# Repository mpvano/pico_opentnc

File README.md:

# PICO_OPENTNC

This is a fork of Peter Filberti's excellent TNC project modified to allow his code to run on the openTNC hardware reference design. This way either firmware can be used on that hardware merely by swapping preprogammed microcontrollers. Note that this fork is for the Pi Pico 2040 only.

# PICO TNC

PICO TNC is the Terminal Node Controler for Amateur Packet Radio powered by Raspberry Pi Pico. This is a fork of that project. I have removed all of the major features of the code except for the modulator/demodulator section and inserted a z80 emulator from my TNCEMU project that emulates a Heathkit HK21 Pocket Packet. Introductory Video can be seen here: https://youtu.be/zq6JLoosqGQ

## PIC TNC features

- Encode and decode Bell 202 AFSK signal without modem chip
- Support USB Serial as well as 3.3v ttl serial interface
- Emulated Support of full tnc and tnc commands including pbbs
- Kiss support at the flip of a switch.
- Operates with open squelch
- TTL Serial Port is configured by emulated TNC parameters when used as a console port.

## Todo
- Add 1600 1800 hz modem for HF Modem support.
- Investigate if FX.25 can be added especially for hf.

## How to build
```
git clone https://github.com/mpvano/pico_opentnc.git
cd pico_opentnc
mkdir build
cd build
cmake ..
make -j4
(flash 'pico_tnc/pico_tnc.uf2' file to your Pico)
```

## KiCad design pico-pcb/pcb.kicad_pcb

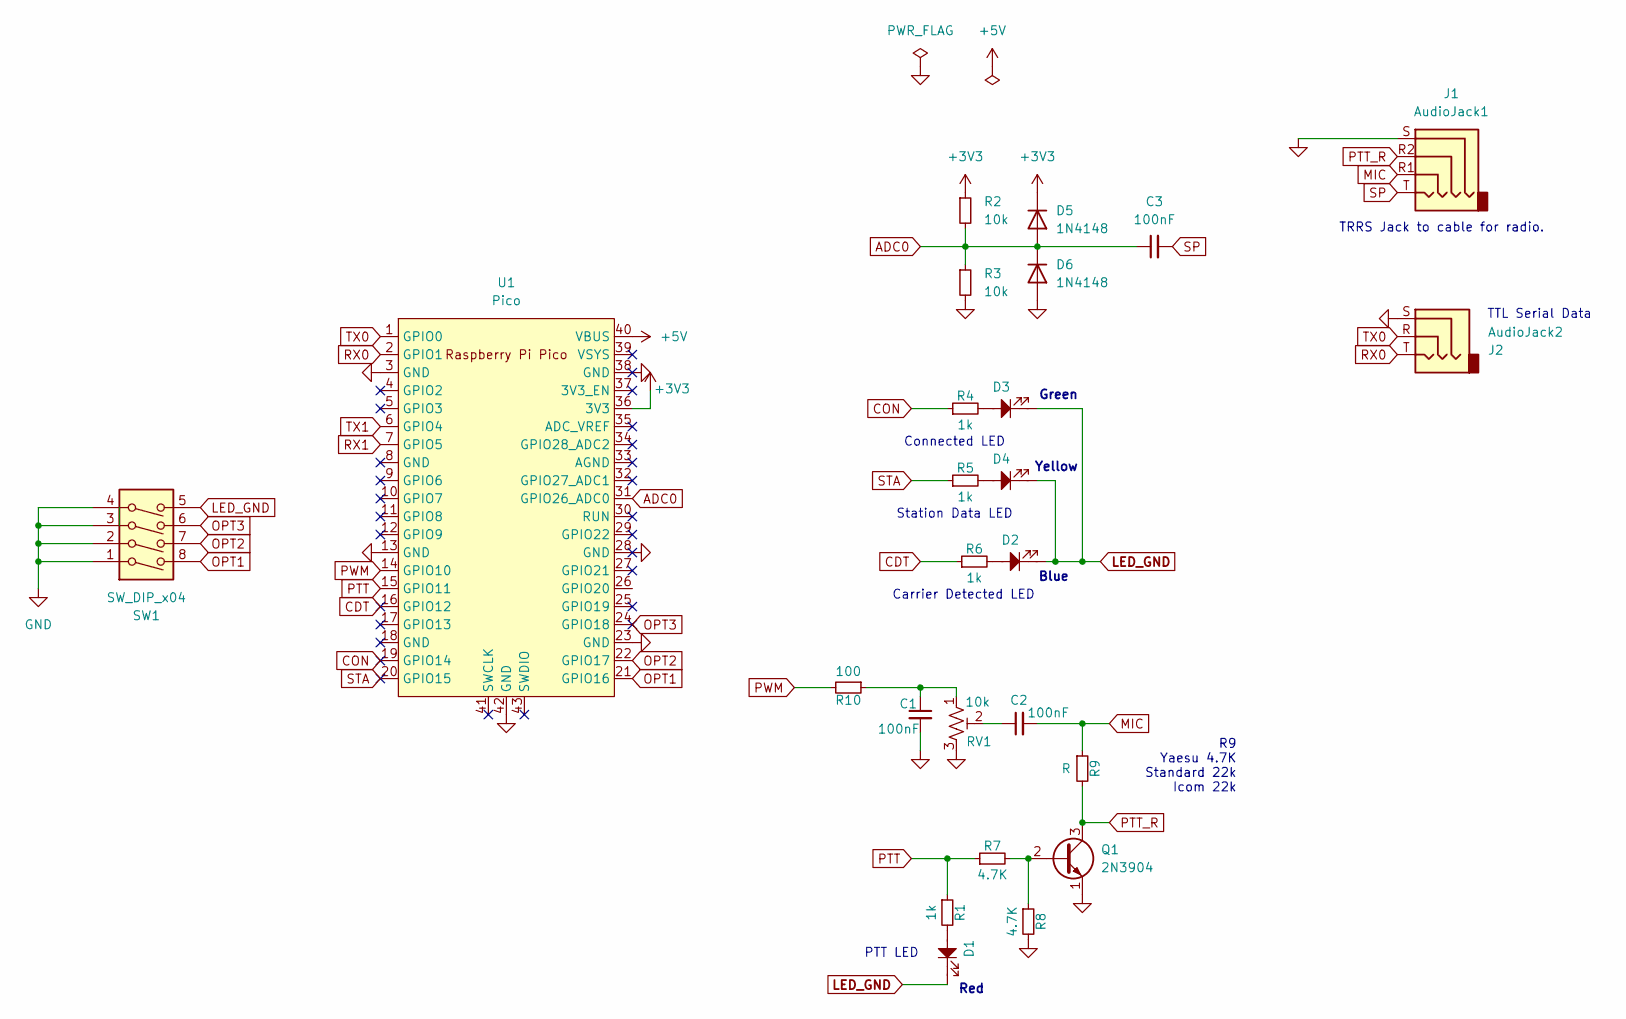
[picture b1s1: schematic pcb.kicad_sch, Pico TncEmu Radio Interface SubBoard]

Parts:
C1, C2, C3: 100nF; C_Disc_D3.0mm_W2.0mm_P2.50mm
D1, D2, D3, D4: LED_3mm; LED_D3.0mm_Horizontal_O1.27mm_Z2.0mm
D5, D6: 1N4148; D_DO-35_SOD27_P7.62mm_Horizontal
J1: AudioJack1; Jack_3.5mm_PJ320D_Horizontal
J2: AudioJack2; PJ-307
Q1: 2N3904; TO-92_Inline
R1, R4, R5, R6: 1k; R_Axial_DIN0204_L3.6mm_D1.6mm_P5.08mm_Horizontal
R2, R3: 10k; R_Axial_DIN0204_L3.6mm_D1.6mm_P5.08mm_Horizontal
R7, R8: 4.7K; R_Axial_DIN0204_L3.6mm_D1.6mm_P5.08mm_Horizontal
R9: R; R_Axial_DIN0204_L3.6mm_D1.6mm_P5.08mm_Horizontal
R10: 100; R_Axial_DIN0204_L3.6mm_D1.6mm_P5.08mm_Horizontal
RV1: 10k; Potentiometer_Runtron_RM-063_Horizontal
SW1: SW_DIP_x04; SW_DIP_SPSTx04_Piano_CTS_Series194-4MSTN_W7.62mm_P2.54mm
U1: Pico; RPi_Pico_SMD_TH

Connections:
+3V3: D5.1 (K), R2.1, U1.36 (3V3)
+5V: U1.40 (VBUS)
ADC0: C3.1, D5.2 (A), D6.1 (K), R2.2, R3.1, U1.31 (GPIO26_ADC0)
CDT: R6.1, U1.16 (GPIO12)
CON: R4.1, U1.19 (GPIO14)
GND: C1.2, D6.2 (A), J1.S, J2.S, Q1.1 (E), R3.2, R8.2, RV1.3, SW1.1, SW1.2, SW1.3, SW1.4, U1.3 (GND), U1.13 (GND), U1.23 (GND), U1.28 (GND), U1.38 (GND), U1.42 (GND)
LED_GND: D1.1, D2.1, D3.1, D4.1, SW1.5
MIC: C2.2, J1.R1, R9.1
unnamed: C1.1, R10.1, RV1.1
unnamed: C2.1, RV1.2
unnamed: D1.2, R1.2
unnamed: D2.2, R6.2
unnamed: D3.2, R4.2
unnamed: D4.2, R5.2
unnamed: Q1.2 (B), R7.2, R8.1
OPT1: SW1.8, U1.21 (GPIO16)
OPT2: SW1.7, U1.22 (GPIO17)
OPT3: SW1.6, U1.24 (GPIO18)
PTT: R1.1, R7.1, U1.15 (GPIO11)
PTT_R: J1.R2, Q1.3 (C), R9.2
PWM: R10.2, U1.14 (GPIO10)
RX0: J2.T, U1.2 (GPIO1)
RX1: U1.7 (GPIO5)
SP: C3.2, J1.T
STA: R5.1, U1.20 (GPIO15)
TX0: J2.R, U1.1 (GPIO0)
TX1: U1.6 (GPIO4)

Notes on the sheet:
PTT LED
Carrier Detected LED
Yellow
Green
TRRS Jack to cable for radio.
Station Data LED
TTL Serial Data
Blue
Connected LED
R9 Yaesu 4.7K Standard 22k Icom 22k
Red

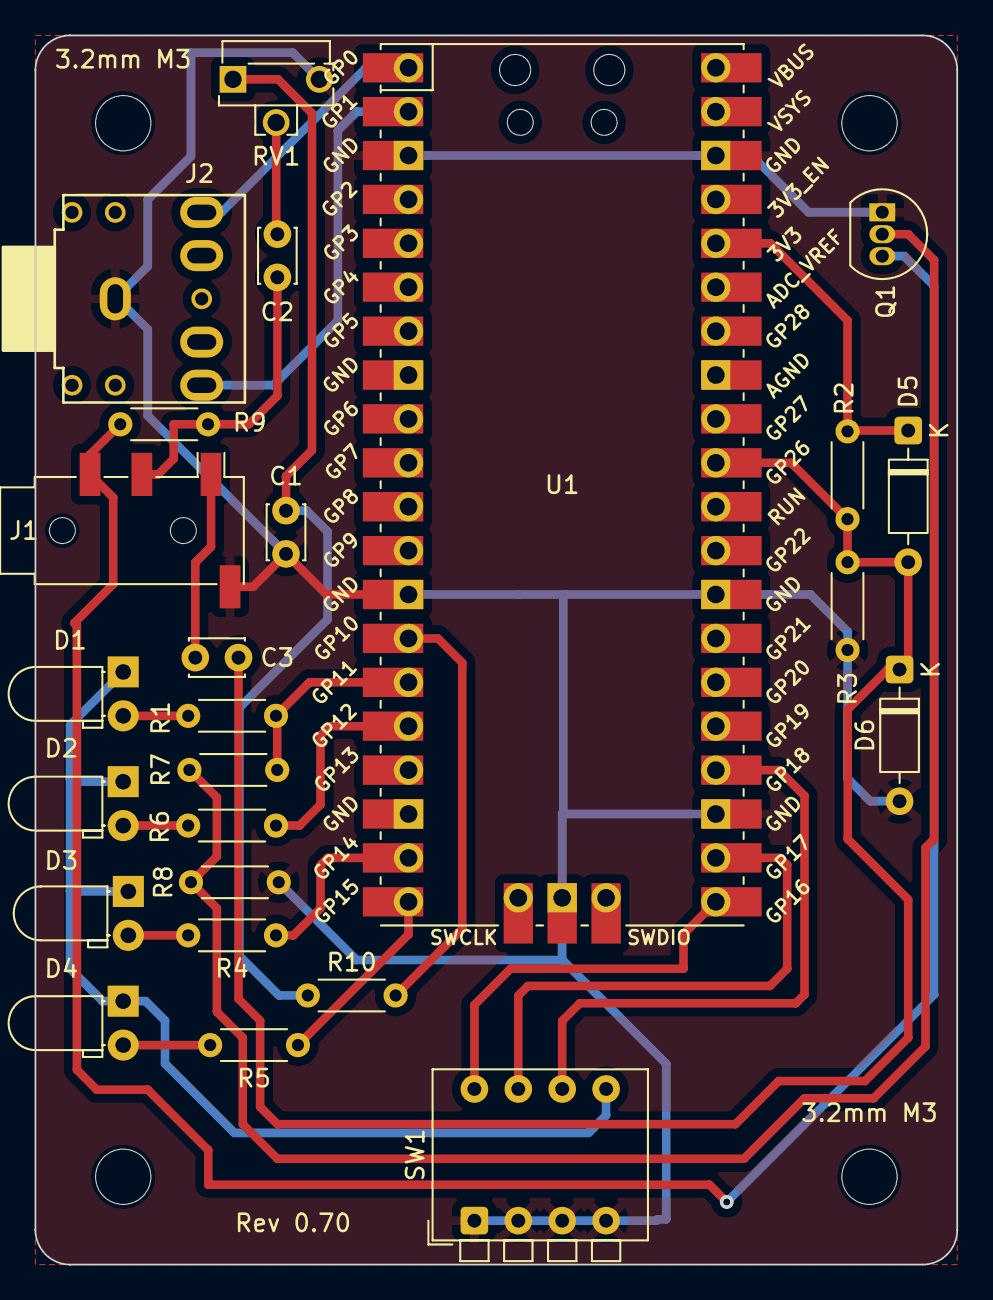
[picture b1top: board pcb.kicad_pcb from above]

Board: 2 copper layers, 53.3 x 71.1 mm, 29 parts (0 on the bottom side), 24 nets.

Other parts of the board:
3.2mm M3, 3.2mm M3#2: MountingHole_3.2mm_M3_ISO14580
 : MountingHole_3.2mm_M3_ISO14580
 #2: MountingHole_3.2mm_M3_ISO14580

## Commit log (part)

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2025-07-29 Modified CMakeLists
2025-07-29 Added tnc emulator Rom image
2025-07-29 Added z80 emulator
2025-07-31 Modified CmakeLists to copy rom object to working dir so binary name references don't include full path!
2025-07-31 Added Preliminary workings of tnc emulator to tnc.c
2025-07-31 Added sio.h header file for emulaition of z80 sio
2025-07-31 in z80emu removed needing to include tnc.h, modified direct access to Rom[] to use Memory_Read_Byte instead
2025-07-31 Removed source files that are not required anymoe and updated CMakeLists.txt
2025-07-31 Plumbed in serial receive/tx through tty mechanism to tncemu. Removed some unnecessary code
2025-08-05 commented out define for GPS_ENABLE
2025-08-05 Updated screenshot
2025-08-06 Added hardware_rtc to target_link_libraries
2025-08-06 Added Ax25 input queue mgt for use by tncemu
2025-08-06 Added code in output_packet to queue the received packet for tncemu, removed counting of received packets */
2025-08-06 Removed unused vars and functions from header file, i.e. AX25 queue functions moved to ax25.c and modified some defines for emulator timings. Modified code in tnc.c to add updating of real time clock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
2025-08-07 Removed test.c and packet_table.c from CMakeLists.txt as they are no longer used.
2025-08-07 Removed unused files packet_table.[ch] and test.[ch]
2025-08-07 Removed TEST_PACKET conditonal from main.c and commented out __wfi() for now to test emulation speed
2025-08-07 Added latest flash file
2025-08-10 Fixed ax25_InQ_Insert to make sure length of packet was incresed by 1 do to how tncemu logic handles packets
2025-08-10 Changed value for MIN_LEN of ax25 packet do to PID byte being optinal
2025-08-12 Modified decode_bit function in decode.c so it can receive more than one frame in a transmission per the ax.25 spec.
2025-08-12 added ax25 parms to TNC struct and modified send to use them as they get set by tnc
2025-08-13 removed no longer needed parm and other structs and cleaned up codebase
2025-08-13 Adde new flash code to be able to write a larger blob of data to flash since we need at least 32768 for to backup the tncemu ram data.
2025-08-13 re-enabled watch dog in main.c
2025-08-13 disabled hardware watchdog during flash writes. fixed bug where ax25_parms where not being fully copied on init.
2025-08-14 Modified flash code to read and write data blobs to different pages so as to do wear leveling of flash device.
2025-08-14 Modified tnc.c to report flash slot that is being written or read from.
2025-08-14 added conled_pin and staled_pin that represent the gpios for the station led and console led. Modified tncemu to track sioa and siob DTR pins on leds as in orginal heathkit hardware.
2025-08-15 Removed unused defines.
2025-08-15 Modified send.c so that txtail is computed based on ax25 parameters set by tnc emulator code KISS_TXTAIL... In the emulator its the AXHANG command that sets it.
2025-08-15 Added frombcd function and cleaned up tobcd. Added code to check year of tncemu clock with pico rtc and if different update the rtc from tnc clock. This allows setting of the pico clock. As long as y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
2025-08-15 Fixed month offset in RTC.
2025-08-15 ADDED Define for MIN_TAIL_FLAGS and inserted into formula.
2025-08-18 Added Kiss support back in with some slight modifications
2025-08-18 added kiss.c to CmakeLists.txt
2025-08-18 Added Kiss support vars to tnc.h
2025-08-18 Changed main.c so that it examines the GPIO KISS_SELECT_GPIO and if set to 0 will go into kiss mode and not process the tnc emulator. If kiss exits with the kiss exit command it will start to emulate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
2025-08-18 Modified kiss.c so it will not exit kiss mode when cmd to do so is received if the kiss selection input is still active.
2025-08-19 Modified flash_read to search for the latest VALID block so that if a block is bad it reverts to the previous known good block to recover tnc emulator ram.
2025-08-21 Changes for IO pin re-assignments for new schematic and pcb
2025-08-21 Updated Schematics
2025-08-21 Updated to latest UF2 file on main dir.
2025-08-21 Updated PCB Images.
2025-08-21 Removed original schematics.
2025-08-22 Updated receive.c to use the gpio led for DCD instead of the on board pico led.
2025-08-24 Added activity timer to tnc.h so that unit sleeps and waits for interrupts when no activity is occuring on tnc emulator. Green on board led on Pico indicates when not sleeping and running full
2025-08-25 Changed DEFAULT_ACTIVITY_COUNT from 1000 to 500 1/2.
2025-08-26 Added Kicad PCB Design.
2025-08-26 Added case design in OpenScad
2025-08-26 Updated PCB Image
2025-08-26 Added case stl file.
2025-08-26 Revised case stl.
2025-08-27 Added CREDIT
2025-08-27 Modified case with options to print either lid or case and optional mounting holes.
2025-08-27 Added some documentation
2025-08-27 Created openscad folder and moved proper items there.
2025-08-27 Changed pbbs welcome msg.
2025-08-27 Update pico uf2
2025-08-27 Updated waveform image
2025-08-28 Restored DEFAULT_ACTIVITY_COUNT back to 1000 as the emulator was not active enough slowing down timeouts etc.
2025-08-28 Update uf2 to latest.
2025-08-28 Removed sio_int timer it is no longer needed. Modified timer_in counter and how often the timer in is called so timings are close to original tnc.
2025-08-28 removed TIMER_TIME_10MS not needed and redefined TIME_1SECOND
2025-08-28 Updated pico uf2
2025-08-28 Removed if condition that was alwas true.
2025-08-29 modified copyright
2025-08-29 modified flash time of led's when in kiss mode
2025-08-29 Updated uf2
2025-08-30 fixed flashing leds for kiss mode
2025-08-30 Fixed clock update time and parm check time in tncemu that caused flash corruption due to it updating flash before tncemu could do its ram checksum. Reorg of main.c so welcome msg is displayed when n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
2025-08-31 Updated case and latest uf2 binary
2025-08-31 Modified openscad file to auto load board image based on if pico height is 0 above pcb or in a socket
2025-09-02 Added stl for pico in socket with header.
2025-09-02 Added Bill of Materials
2025-09-03 Updated Bom with warning about using Pico instead of Pico2
2025-09-03 Made lettering a little deeper. Raised the case to insure lid clears usb connector.
2025-09-03 Updated case stl and added lid.
2025-09-04 Modified tnc.c to blink sta led when a new msg has arrived in the pbbs mailbox. Clears when op hits return or on reboot. Updated uf2 binary
2025-09-04 Modofied tnc.c to only set newMsg if the next bbs msg # is > than previous. This avoids false newmsg indications when a message is removed. Updated uf2 binary
2025-09-04 Added short tnc case for when pico is soldered directly to pcb.
2025-09-05 fixed bug where conled update was removed from tnc.c
2025-09-05 updated uf2 binary
2025-09-05 Made openscad script customizer friendly.
2025-09-13 opensquelch changes
2025-09-16 Added OPEN_SQUELCH define in tnc.h so that the option can be compiled in or out. Modified decode.c so that when in open squelch if there is no energy it resets reciver state to flag and disables cdt 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
2025-09-16 Update README.md
    Operates with open squelch feature added
2025-09-16 Updated schematic with new pinning on trrs jack to make it digirig cable compatible.
2025-09-17 Updated schematic png/jpg
2025-09-17 Updated binary uf2 file with latest open squelch build.
2025-09-18 Updated PCB .50mm traces now and rewired trrs jack to match digirig type cabling.
2025-09-18 Updated tnc commands text file.
2025-09-19 Modified main.c so that it only waits 10 seconds for usb connection to appear and then it just continues and launches tnc emulation etc. Also added test for dip switch if enabled jumps into bootloade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
2025-09-19 Added photo of tnc in case.
2025-09-19 Update README.md
    Added case photo
2025-09-23 modified name of dip switch inputs
2025-09-23 modified kiss.c so kiss ff command never exits kiss mode, modified main.c to read dip switch mode settings and configure input channels based on dip switch. Added functions to tnc.c to send output to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
2025-09-23 Added console output routines to tnc so output only goes to port configured as a console. Modified main.c to send msgs to consoles only. Modified tnc.c to send ax25 packet to any kiss ports before re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
2025-09-23 updated dev build binary
2025-09-23 Added dip switch mode CON_MSG
2025-09-24 modified main.c to only sleep when tnc emulator is not busy
2025-09-24 modified tnc.c to send ax25 packets received to kiss ports before unqueue in emulator. Fixed some bugs where we were referencing ttys as a pointer instead of direct
2025-09-25 Reversed dip switch logic.
2025-09-25 Modified to only send kiss packets to usb port if usb is connected.
2025-09-25 Updated uf2 binary.
2025-09-25 Changed DIP OPTIONS
2025-09-25 Added function Read_Dip_Switch to read the dip switch bits. Modified so dip is checked every second and if a change occurs it will reboot so new change can take effect. Updated UF2 Binary
2025-09-25 Modified file modes
2025-09-28 Modifed tnc emulator rom image so main pbbs prompt ends with a : instead of > to match other prompts
2025-09-28 Modified main.c so that if either ports are in console mode it waits 5 seconds so there is time to show greeting, update tnc.uf2 binary
2025-09-29 Start of Manual in ODT format
2025-09-29 Manual formatting edits
2025-09-30 Edits to manual
2025-09-30 Tnc Manual edits
2025-10-02 Tnc Manual edits and added pdf version
2025-10-02 Tnc Manual edits added TOC and Command Index and updated pdf version
2025-10-02 Tnc Manual edits and updated pdf version
2025-10-03 Tnc Manual added LED info and updated pdf version
2025-10-03 Tnc Manual added assembly guide and updated pdf version
2025-10-03 Tnc Manual added PBBS Info and updated pdf version
2025-10-04 Restored BBS prompt to > for compatability
2025-10-05 Updated latest binary uf2 file
2025-10-08 Prelim v.50 Uart Serial TTL Port now will change speeds and parameters like parity and wordlen to match settings in tnc emulator only if port is used as console, for kiss it remains at 115200 baud
2025-10-08 Fixed setting of wrong parm in case statement
2025-10-09 Repaired stupid bug in tnc.c where we were listening to io reads of ctc instead of writes to determine serial port baud rate change. Updated binary .uf2
2025-10-09 Tnc Manual edits and updated pdf version. Added pcb files and ackups
2025-10-09 untracked vscode file
2025-10-09 Modified schematic to reflect dip switch labels
2025-10-20 Added SIO interrupt processing timing as per original TNCEMU. Modified so that minimum txdelay is set to MIN_TNCEMU_TXDELAY. Added that define to tnc.h
2025-10-20 fixed typo in tnc.h
2025-10-21 Bumped version in main.c, removed forced setting of txdelay in tnc.c on power up as this caused a bbram checksum failure when tnc launched. Removed VERSION Define in tnc.h
2025-10-21 Update Manual to explain autobaud on first power up
2025-10-21 Updated binary .uf2 file
2025-10-21 Wrapped debug code with conditional compile
2025-11-03 Update Manual to explain how to save tnc parameters using TXDELAY
2025-11-10 Update README.md
    Added link to introductory video
2025-11-18 Updated Schematic and PCB to add 100ohm resistor to pwm circuit as per original pico tnc and recommendation by Mario AE0GL
2025-11-18 Modified manual to reflect new oshpark pcb location
2025-11-19 Generated NC drill files for pcb fabrication
2025-11-25 Updated Manual BOM with missing transistor entry
2025-12-01 Updated Manual Page 87 with Jack part# details
2025-12-01 Added open scad filefor short case. Modified to set adjustment pot hole as parameter
2025-12-02 explanation of the purpose of the fork
    Fork of Pfilberti's excellent TNC Project with pinout changes to allow his code to run on the OpenTNC reference Hardware PCB.
2025-12-02 modified files to allow GPIO changes for openTNC
    Modified header file with definitions for GPIO pins and new send and receive files to use them
